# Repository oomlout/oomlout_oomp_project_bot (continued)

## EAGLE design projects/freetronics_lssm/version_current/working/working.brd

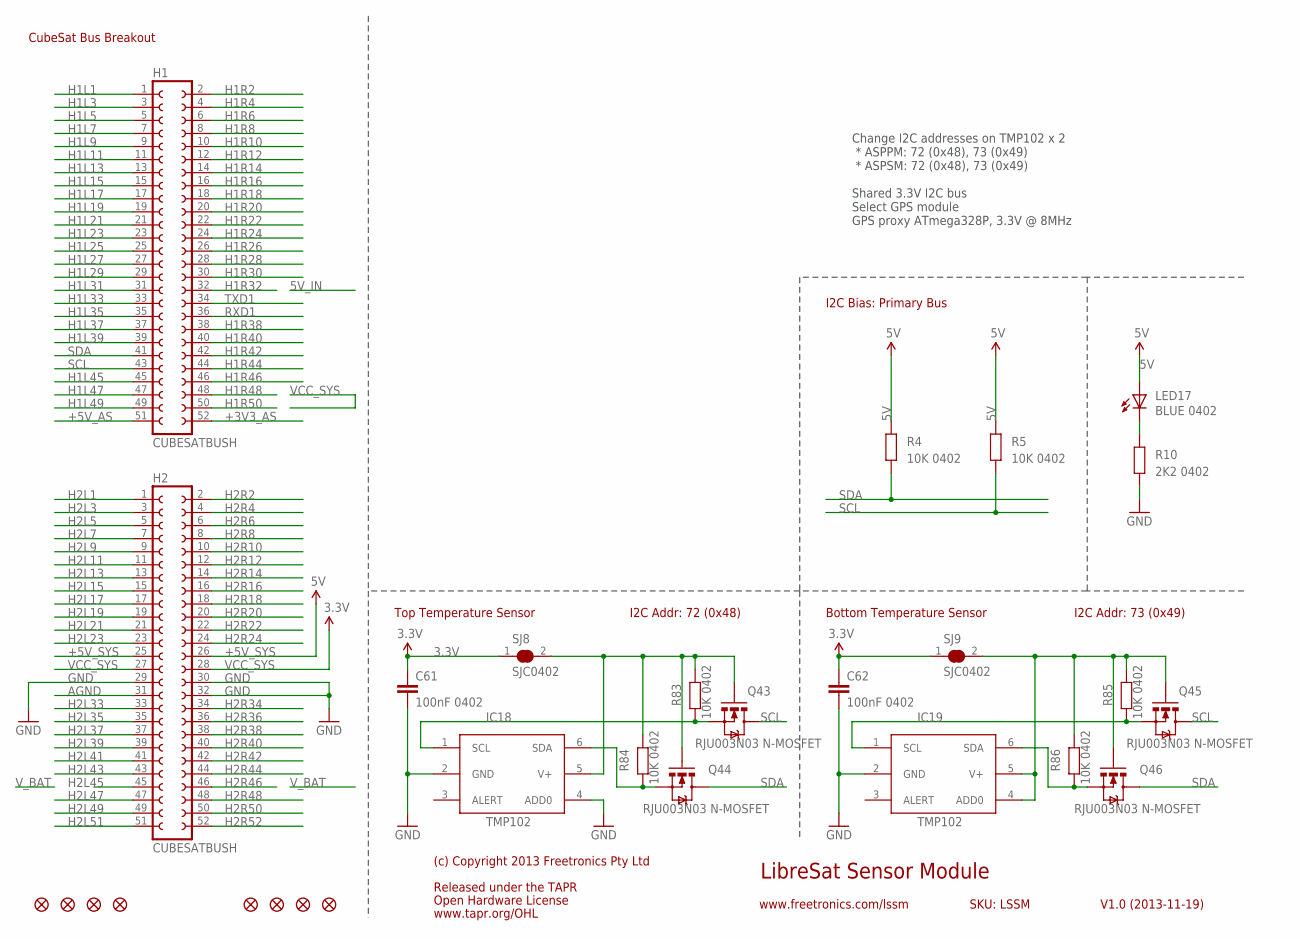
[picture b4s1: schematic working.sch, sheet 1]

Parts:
C61, C62: 100nF 0402; 0402C
FID1, FID2, FID3, FID4, FID5, FID6, FID7, FID8: FIDUCIAL1X2.5; FIDUCIAL-1X2.5
H1, H2: CUBESATBUSH; CUBESATBUS
IC18, IC19: TMP102; SOT563
LED17: BLUE 0402; LED-0402
Q43, Q44, Q45, Q46: RJU003N03 N-MOSFET; SOT32-3
R4, R5, R83, R84, R85, R86: 10K 0402; 0402
R10: 2K2 0402; 0402
SJ8, SJ9: SJC0402; 0402SJC

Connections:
3.3V: C61.1, C62.1, SJ8.1, SJ9.1; also elsewhere on the board
5V: LED17.A, R4.2, R5.2; also elsewhere on the board
+3V3_AS: H1.52
+5V_AS: H1.51
+5V_SYS: H2.25, H2.26
AGND: H2.31
GND: C61.2, C62.2, H2.29, H2.30, H2.32, IC18.2 (GND), IC18.4 (ADD0), IC19.2 (GND), R10.1; also elsewhere on the board
H1L1: H1.1
H1L3: H1.3
H1L5: H1.5
H1L7: H1.7
H1L9: H1.9
H1L11: H1.11
H1L13: H1.13
H1L15: H1.15
H1L17: H1.17
H1L19: H1.19
H1L21: H1.21
H1L23: H1.23
H1L25: H1.25
H1L27: H1.27
H1L29: H1.29
H1L31: H1.31
H1L33: H1.33
H1L35: H1.35
H1L37: H1.37
H1L39: H1.39
H1L45: H1.45
H1L47: H1.47
H1L49: H1.49
H1R2: H1.2
H1R4: H1.4
H1R6: H1.6
H1R8: H1.8
H1R10: H1.10
H1R12: H1.12
H1R14: H1.14
H1R16: H1.16
H1R18: H1.18
H1R20: H1.20
H1R22: H1.22
H1R24: H1.24
H1R26: H1.26
H1R28: H1.28
H1R30: H1.30
H1R32: H1.32
H1R38: H1.38
H1R40: H1.40
H1R42: H1.42
H1R44: H1.44
H1R46: H1.46
H1R48: H1.48
H1R50: H1.50
H2L1: H2.1
H2L3: H2.3
H2L5: H2.5
H2L7: H2.7
H2L9: H2.9
H2L11: H2.11
H2L13: H2.13
H2L15: H2.15
H2L17: H2.17
H2L19: H2.19
H2L21: H2.21
H2L23: H2.23
H2L33: H2.33
H2L35: H2.35
H2L37: H2.37
H2L39: H2.39
H2L41: H2.41
H2L43: H2.43
H2L45: H2.45
H2L47: H2.47
H2L49: H2.49
H2L51: H2.51
H2R2: H2.2
H2R4: H2.4
H2R6: H2.6
H2R8: H2.8
H2R10: H2.10
H2R12: H2.12
H2R14: H2.14
H2R16: H2.16
H2R18: H2.18
H2R20: H2.20
H2R22: H2.22
H2R24: H2.24
H2R34: H2.34
H2R36: H2.36
H2R38: H2.38
H2R40: H2.40
H2R42: H2.42
H2R44: H2.44
H2R46: H2.46
H2R48: H2.48
H2R50: H2.50
H2R52: H2.52
unnamed: LED17.C, R10.2
unnamed: IC18.1 (SCL), Q43.2 (S), R83.1
unnamed: IC18.6 (SDA), Q44.2 (S), R84.1
unnamed: IC19.6 (SDA), Q46.2 (S), R86.1
unnamed: IC19.1 (SCL), Q45.2 (S), R85.1
unnamed: IC18.5 (V+), Q43.1 (G), Q44.1 (G), R83.2, R84.2, SJ8.2
unnamed: IC19.4 (ADD0), IC19.5 (V+), Q45.1 (G), Q46.1 (G), R85.2, R86.2, SJ9.2
RXD1: H1.36; also elsewhere on the board
SCL: H1.43, Q43.3 (D), Q45.3 (D), R5.1; also elsewhere on the board
SDA: H1.41, Q44.3 (D), Q46.3 (D), R4.1; also elsewhere on the board
TXD1: H1.34; also elsewhere on the board
VCC_SYS: H2.27, H2.28

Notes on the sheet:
LibreSat Sensor Module
V1.0 (2013-11-19)
www.freetronics.com/lssm
SKU: LSSM
CubeSat Bus Breakout
Released under the TAPR
Open Hardware License
www.tapr.org/OHL
(c) Copyright 2013 Freetronics Pty Ltd
I2C Bias: Primary Bus
Top Temperature Sensor
Bottom Temperature Sensor
I2C Addr: 72 (0x48)
I2C Addr: 73 (0x49)
Change I2C addresses on TMP102 x 2 * ASPPM: 72 (0x48), 73 (0x49) * ASPSM: 72 (0x48), 73 (0x49) Shared 3.3V I2C bus Select GPS module GPS proxy ATmega328P, 3.3V @ 8MHz

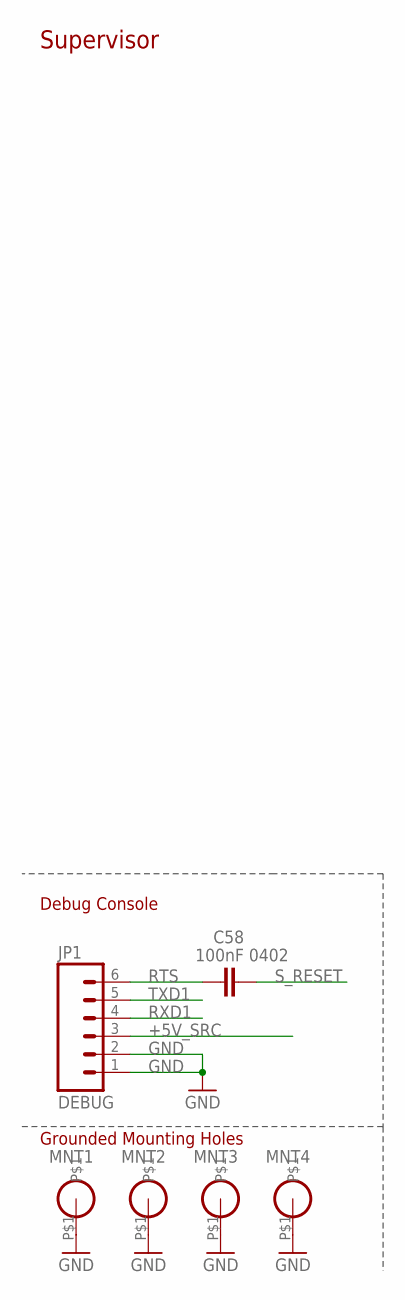
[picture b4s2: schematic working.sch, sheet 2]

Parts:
C58: 100nF 0402; 0402C
JP1: DEBUG; MOLEX-1X6-RA
MNT1, MNT2, MNT3, MNT4: HOLE3.2MM; HOLE32

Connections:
+5V_SRC: JP1.3
GND: JP1.1, JP1.2, MNT1.P$1, MNT2.P$1, MNT3.P$1, MNT4.P$1; also elsewhere on the board
RTS: C58.1, JP1.6
RXD1: JP1.4; also elsewhere on the board
S_RESET: C58.2
TXD1: JP1.5; also elsewhere on the board

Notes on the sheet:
Supervisor
Grounded Mounting Holes
Debug Console

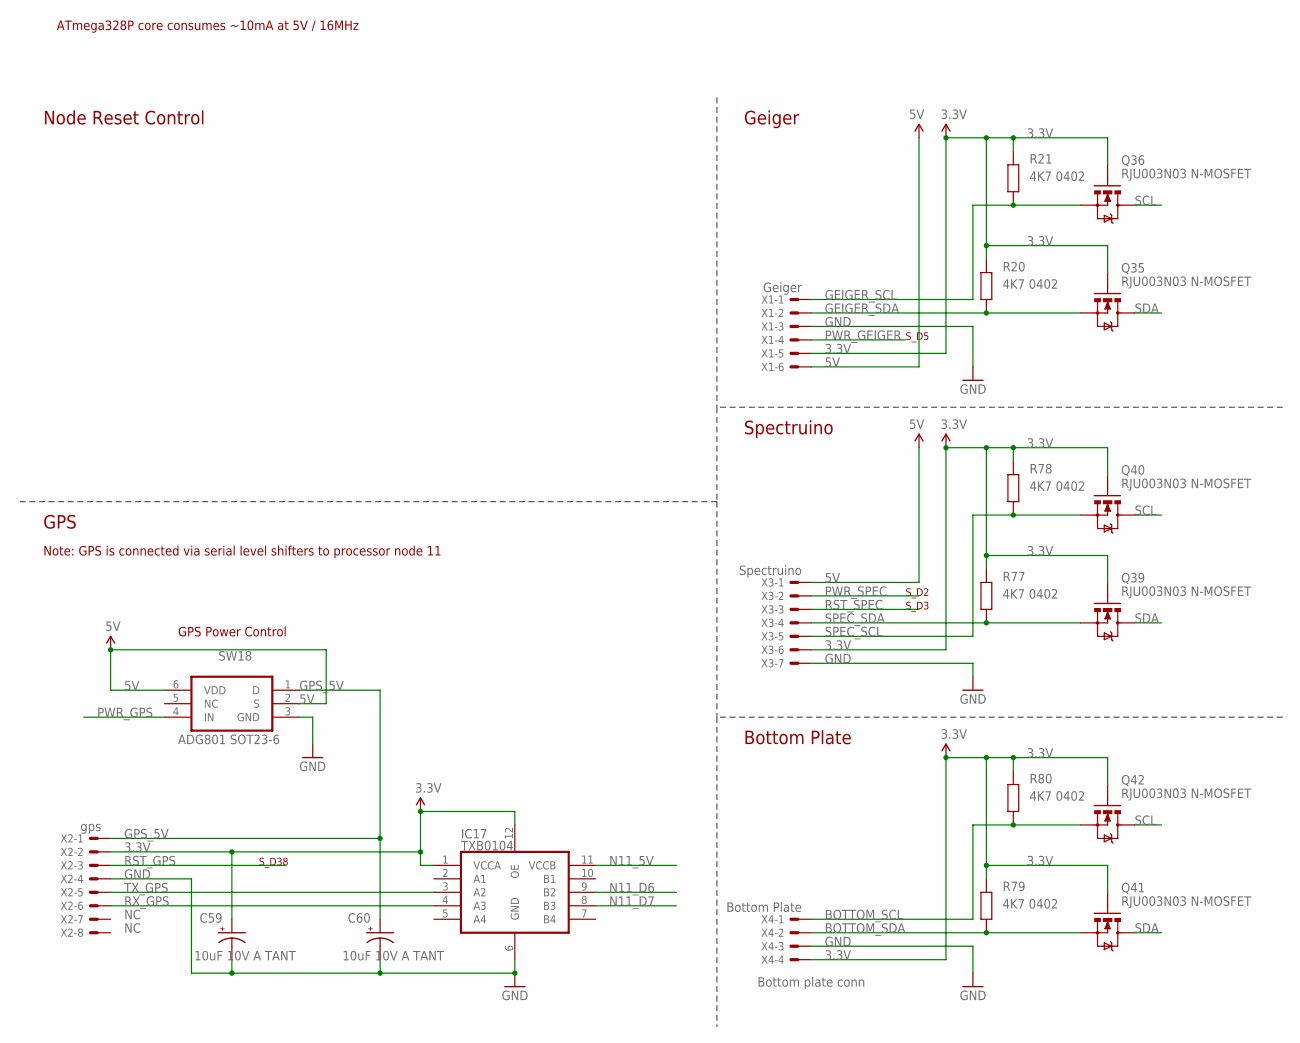
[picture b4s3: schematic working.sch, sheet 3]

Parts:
C59, C60: 10uF 10V A TANT; EIA3216
IC17: TXB0104; QFN-12
Q35, Q36, Q39, Q40, Q41, Q42: RJU003N03 N-MOSFET; SOT32-3
R20, R21, R77, R78, R79, R80: 4K7 0402; 0402
SW18: ADG801 SOT23-6; SOT23-6
X1: Geiger; 53398-06
X2: gps; 53398-08
X3: Spectruino; 53398-07
X4: Bottom Plate; 53398-04

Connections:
3.3V: C59.A (+), IC17.1 (VCCA), IC17.12 (OE), Q35.1 (G), Q36.1 (G), Q39.1 (G), Q40.1 (G), Q41.1 (G), Q42.1 (G), R20.2, R21.2, R77.2, R78.2, R79.2, R80.2, X1.5, X2.2, X3.6, X4.4; also elsewhere on the board
5V: SW18.2 (S), SW18.6 (VDD), X1.6, X3.1; also elsewhere on the board
BOTTOM_SCL: Q42.2 (S), R80.1, X4.1
BOTTOM_SDA: Q41.2 (S), R79.1, X4.2
GEIGER_SCL: Q36.2 (S), R21.1, X1.1
GEIGER_SDA: Q35.2 (S), R20.1, X1.2
GND: C59.C (-), C60.C (-), IC17.6 (GND), SW18.3 (GND), X1.3, X2.4, X3.7, X4.3; also elsewhere on the board
GPS_5V: C60.A (+), SW18.1 (D), X2.1
N11_5V: IC17.11 (VCCB); also elsewhere on the board
N11_D6: IC17.9 (B2); also elsewhere on the board
N11_D7: IC17.8 (B3); also elsewhere on the board
PWR_GEIGER: X1.4
PWR_GPS: SW18.4 (IN)
PWR_SPEC: X3.2
RST_GPS: X2.3
RST_SPEC: X3.3
RX_GPS: IC17.4 (A3), X2.6
SCL: Q36.3 (D), Q40.3 (D), Q42.3 (D); also elsewhere on the board
SDA: Q35.3 (D), Q39.3 (D), Q41.3 (D); also elsewhere on the board
SPEC_SCL: Q40.2 (S), R78.1, X3.5
SPEC_SDA: Q39.2 (S), R77.1, X3.4
TX_GPS: IC17.3 (A2), X2.5

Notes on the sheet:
Node Reset Control
Bottom plate conn
Geiger
Spectruino
Bottom Plate
GPS
Note: GPS is connected via serial level shifters to processor node 11
S_D3
S_D2
S_D5
ATmega328P core consumes ~10mA at 5V / 16MHz
S_D38
GPS Power Control

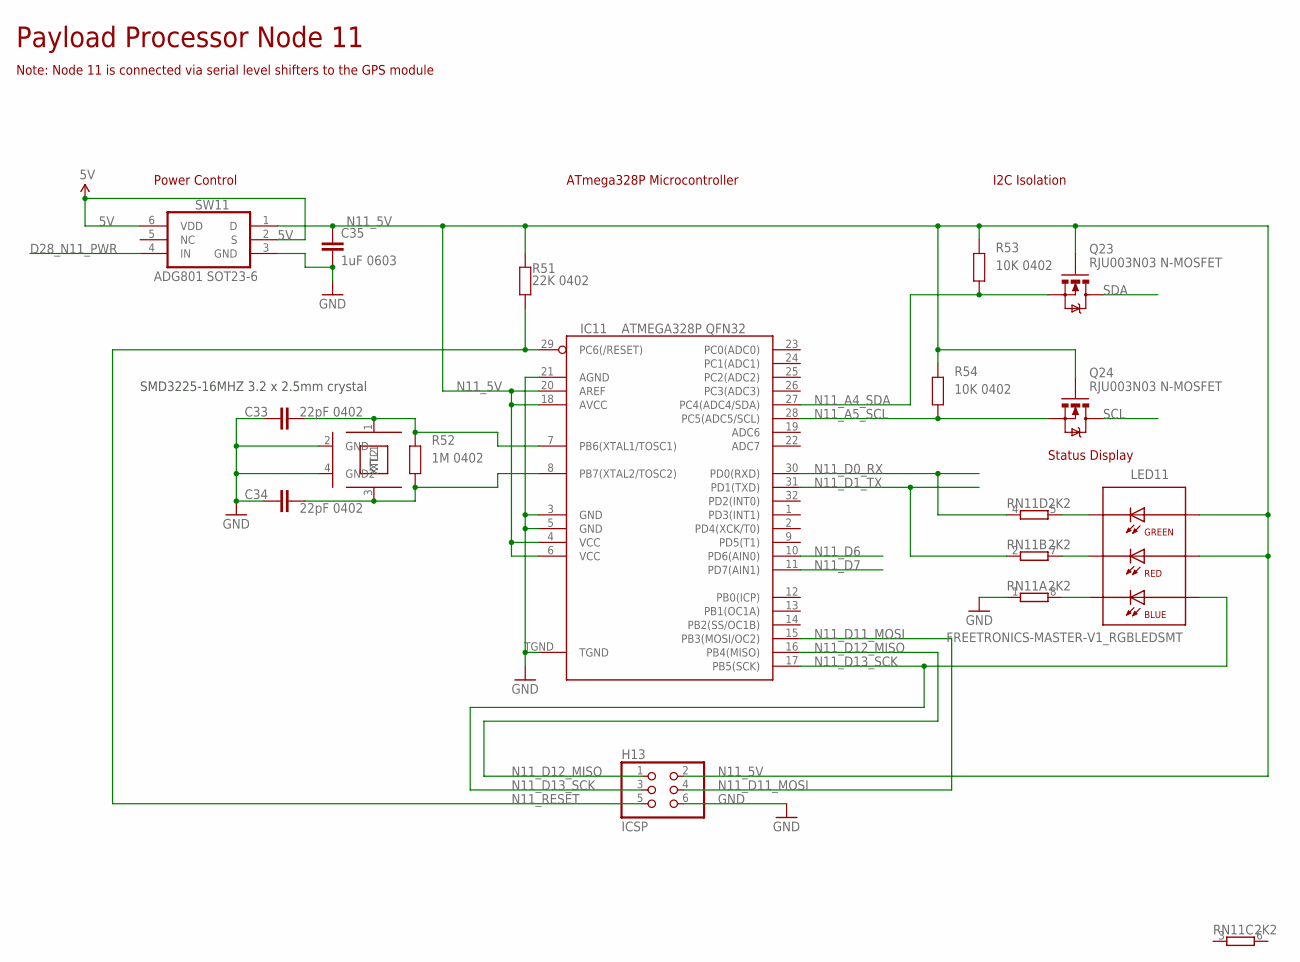
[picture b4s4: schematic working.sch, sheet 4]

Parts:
C33, C34: 22pF 0402; 0402C
C35: 1uF 0603; C0603
H13: ICSP; M2X3-2MM
IC11: ATMEGA328P QFN32; MLF32
LED11: FREETRONICS-MASTER-V1_RGBLEDSMT; FREETRONICS-MASTER-V1_19-337
Q23, Q24: RJU003N03 N-MOSFET; SOT32-3
R51: 22K 0402; 0402
R52: 1M 0402; 0402
R53, R54: 10K 0402; 0402
RN11: 2K2; CAY16
SW11: ADG801 SOT23-6; SOT23-6
XTL11: SMD3225-8MHZ 3.2 x 2.5mm crystal; CRYSTAL-SMD-3X2

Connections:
5V: SW11.2 (S), SW11.6 (VDD); also elsewhere on the board
D28_N11_PWR: SW11.4 (IN)
GND: C33.1, C34.1, C35.2, H13.6, IC11.3 (GND), IC11.5 (GND), IC11.21 (AGND), IC11.TGND, RN11.1, SW11.3 (GND), XTL11.2 (GND), XTL11.4 (GND2); also elsewhere on the board
N11_5V: C35.1, H13.2, IC11.4 (VCC), IC11.6 (VCC), IC11.18 (AVCC), IC11.20 (AREF), LED11.5 (A-R), LED11.6 (A-G), Q23.1 (G), Q24.1 (G), R51.2, R53.2, R54.2, SW11.1 (D); also elsewhere on the board
N11_A4_SDA: IC11.27 (PC4(ADC4/SDA)), Q23.2 (S), R53.1
N11_A5_SCL: IC11.28 (PC5(ADC5/SCL)), Q24.2 (S), R54.1
N11_D0_RX: IC11.30 (PD0(RXD)), RN11.4 (1)
N11_D1_TX: IC11.31 (PD1(TXD)), RN11.2 (1)
N11_D6: IC11.10 (PD6(AIN0)); also elsewhere on the board
N11_D7: IC11.11 (PD7(AIN1)); also elsewhere on the board
N11_D11_MOSI: H13.4, IC11.15 (PB3(MOSI/OC2))
N11_D12_MISO: H13.1, IC11.16 (PB4(MISO))
N11_D13_SCK: H13.3, IC11.17 (PB5(SCK)), LED11.4 (A-B)
N11_RESET: H13.5, IC11.29 (PC6(/RESET)), R51.1
unnamed: C34.2, IC11.8 (PB7(XTAL2/TOSC2)), R52.1, XTL11.3 (XTL2)
unnamed: C33.2, IC11.7 (PB6(XTAL1/TOSC1)), R52.2, XTL11.1 (XTL1)
unnamed: LED11.2 (C-R), RN11.7 (2)
unnamed: LED11.1 (C-B), RN11.8 (2)
unnamed: LED11.3 (C-G), RN11.5 (2)
SCL: Q24.3 (D); also elsewhere on the board
SDA: Q23.3 (D); also elsewhere on the board

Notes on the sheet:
Payload Processor Node 11
ATmega328P Microcontroller
I2C Isolation
Status Display
Power Control
SMD3225-16MHZ 3.2 x 2.5mm crystal
Note: Node 11 is connected via serial level shifters to the GPS module

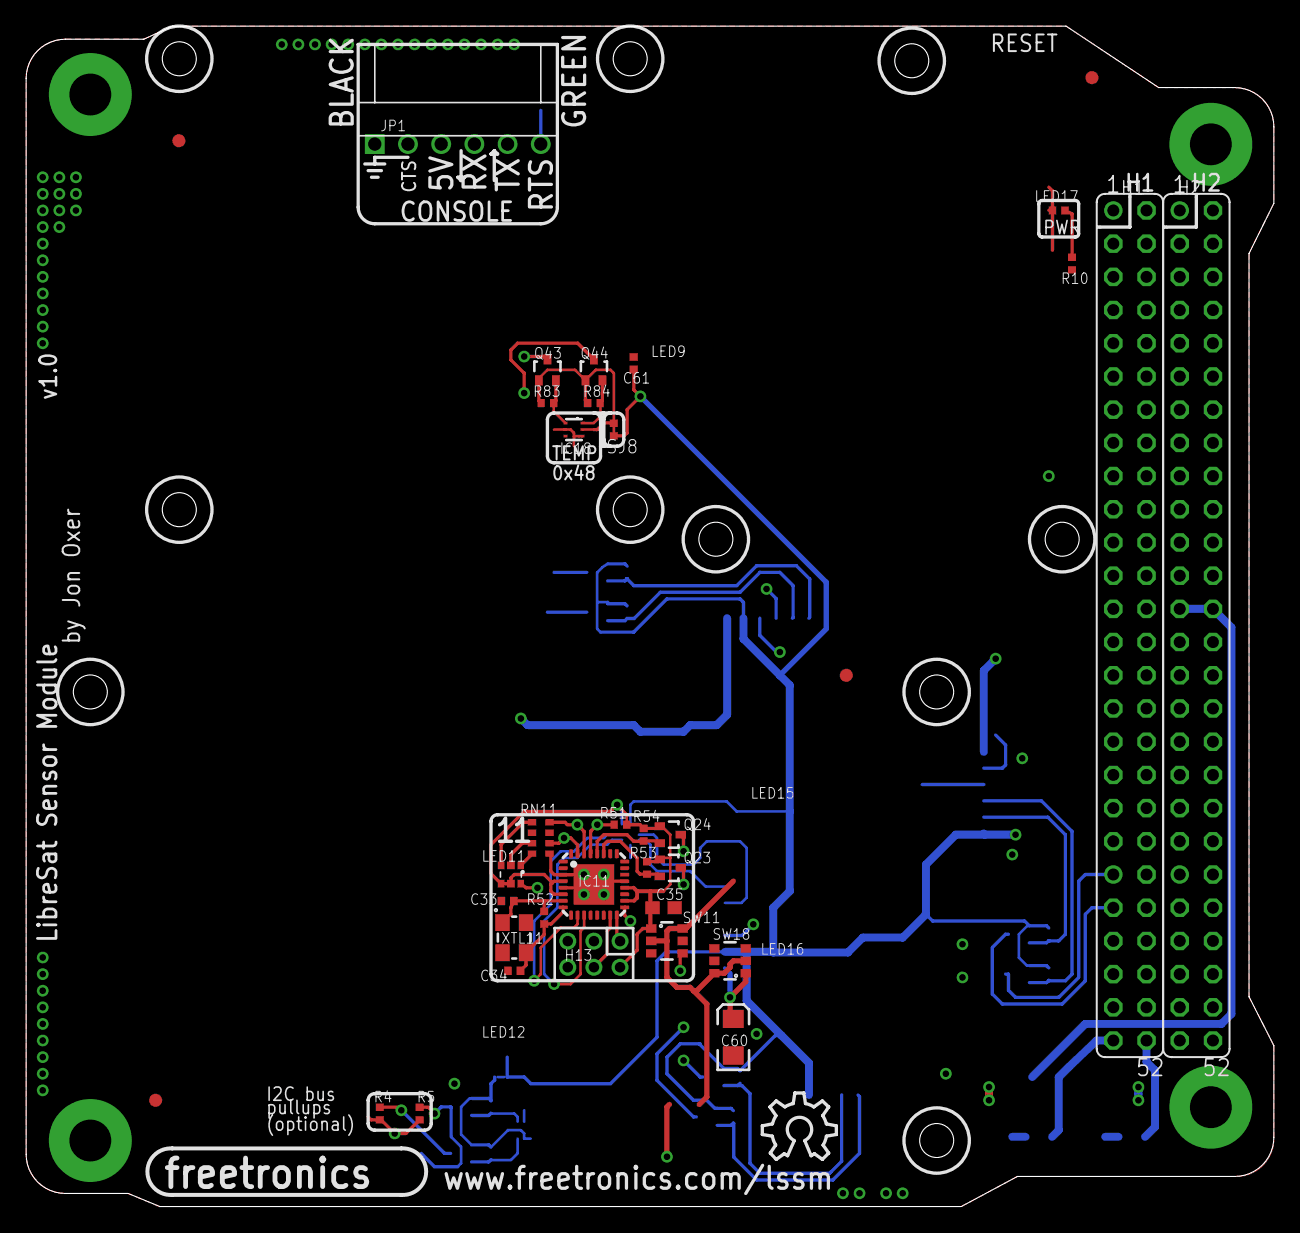
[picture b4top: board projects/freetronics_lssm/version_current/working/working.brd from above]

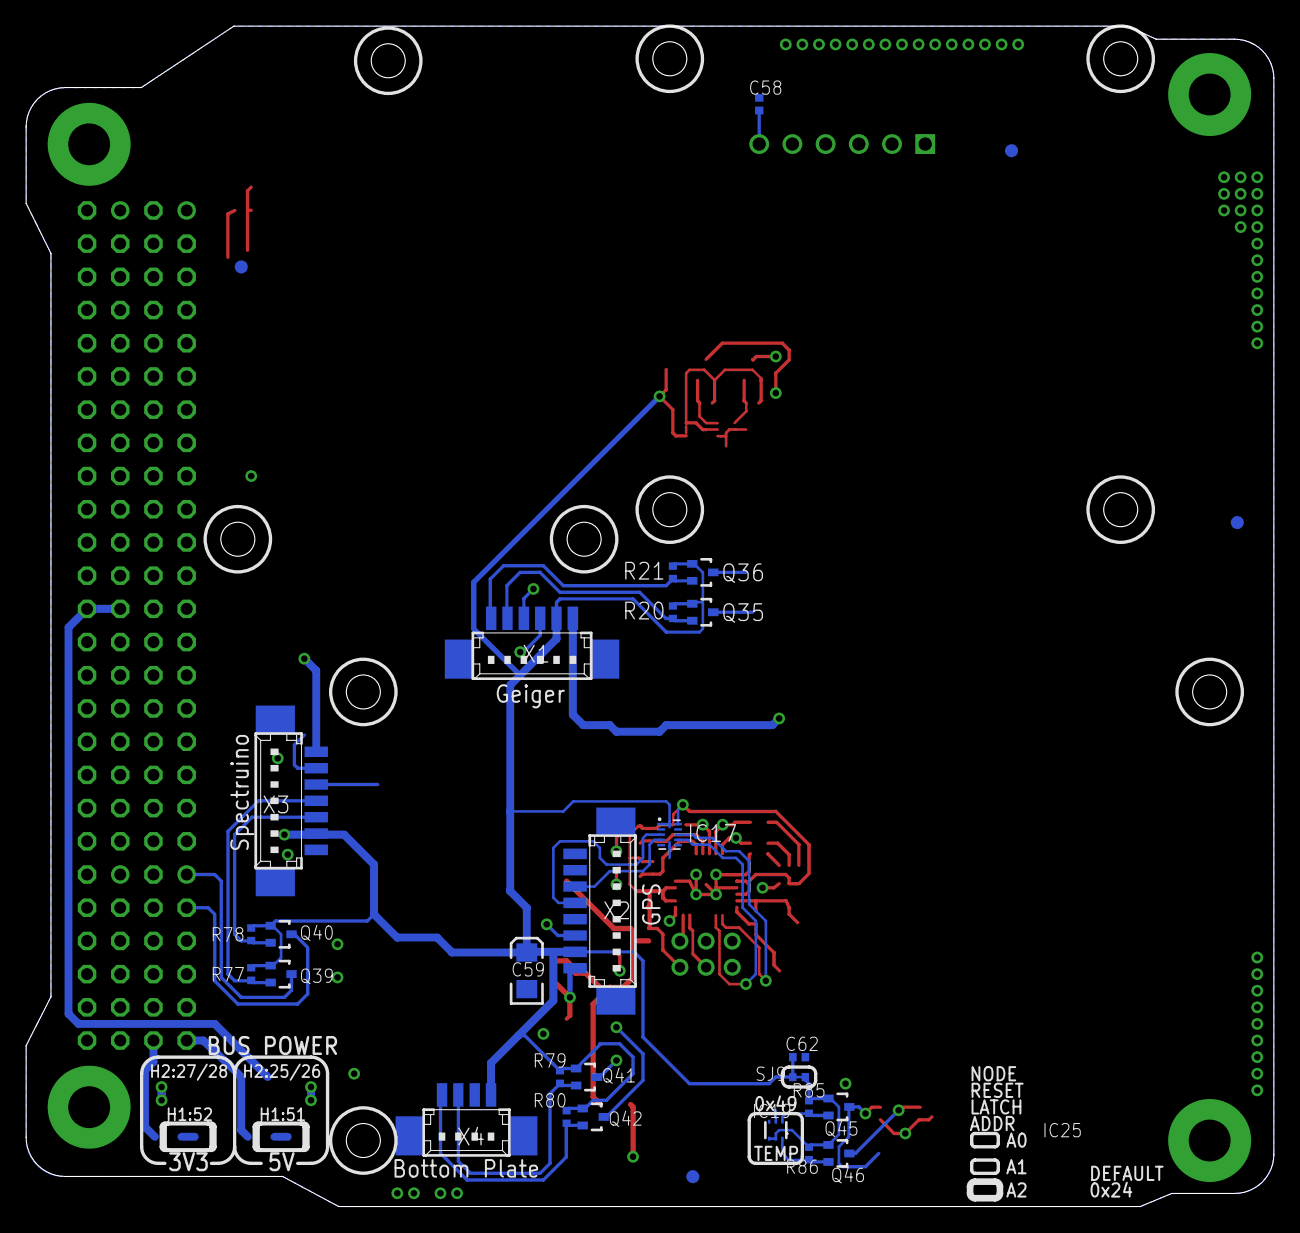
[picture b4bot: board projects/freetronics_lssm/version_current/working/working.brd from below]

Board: 4 copper layers, 95.5 x 90.3 mm, 70 parts (30 on the bottom side), 42 nets.

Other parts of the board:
U$33: OSHW_10X200_NOTEXT

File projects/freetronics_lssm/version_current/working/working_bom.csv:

"Id";"Designator";"Footprint";"Quantity";"Designation";"Supplier and ref";
1;"Q23,Q44,Q43,Q24,Q42,Q36,Q46,Q35,Q41,Q40,Q39,Q45";"SOT32-3";12;"RJU003N03 N-MOSFET";;;
2;"RN11";"CAY16";1;"2K2";;;
3;"MNT1,MNT2,MNT3,MNT4";"HOLE32";4;"HOLE3.2MM";;;
4;"@HOLE6,@HOLE5,@HOLE9,@HOLE4,@HOLE2,@HOLE3,@HOLE8,@HOLE7,@HOLE1,@HOLE0";"";10;"";;;
5;"R53,R5,R54,R84,R83,R4,R85,R86";"0402";8;"10K 0402";;;
6;"C60,C59";"EIA3216";2;"10uF 10V A TANT";;;
7;"LED11";"FREETRONICS-MASTER-V1_19-337";1;"FREETRONICS-MASTER-V1_RGBLEDSMT";;;
8;"R52";"0402";1;"1M 0402";;;
9;"C35";"C0603";1;"1uF 0603";;;
10;"IC18,IC19";"SOT563";2;"TMP102";;;
11;"LED17";"LED-0402";1;"BLUE 0402";;;
12;"FID2,FID4,FID1,FID3,FID8,FID5,FID7,FID6";"FIDUCIAL-1X2.5";8;"FIDUCIAL1X2.5";;;
13;"SW18,SW11";"SOT23-6";2;"ADG801 SOT23-6";;;
14;"C61,C62,C58";"0402C";3;"100nF 0402";;;
15;"H1,H2";"CUBESATBUS";2;"CUBESATBUSH";;;
16;"XTL11";"CRYSTAL-SMD-3X2";1;"SMD3225-8MHZ 3.2 x 2.5mm crystal";;;
17;"C34,C33";"0402C";2;"22pF 0402";;;
18;"R51";"0402";1;"22K 0402";;;
19;"H13";"M2X3-2MM";1;"ICSP";;;
20;"R10";"0402";1;"2K2 0402";;;
21;"SJ8,SJ9";"0402SJC";2;"SJC0402";;;
22;"JP1";"MOLEX-1X6-RA";1;"DEBUG";;;
23;"U$33";"OSHW_10X200_NOTEXT";1;"";;;
24;"IC11";"MLF32";1;"ATMEGA328P QFN32";;;
25;"R21,R80,R79,R78,R20,R77";"0402";6;"4K7 0402";;;
26;"X1";"53398-06";1;"Geiger";;;
27;"X4";"53398-04";1;"Bottom Plate";;;
28;"IC17";"QFN-12";1;"TXB0104";;;
29;"X2";"53398-08";1;"gps";;;
30;"X3";"53398-07";1;"Spectruino";;;

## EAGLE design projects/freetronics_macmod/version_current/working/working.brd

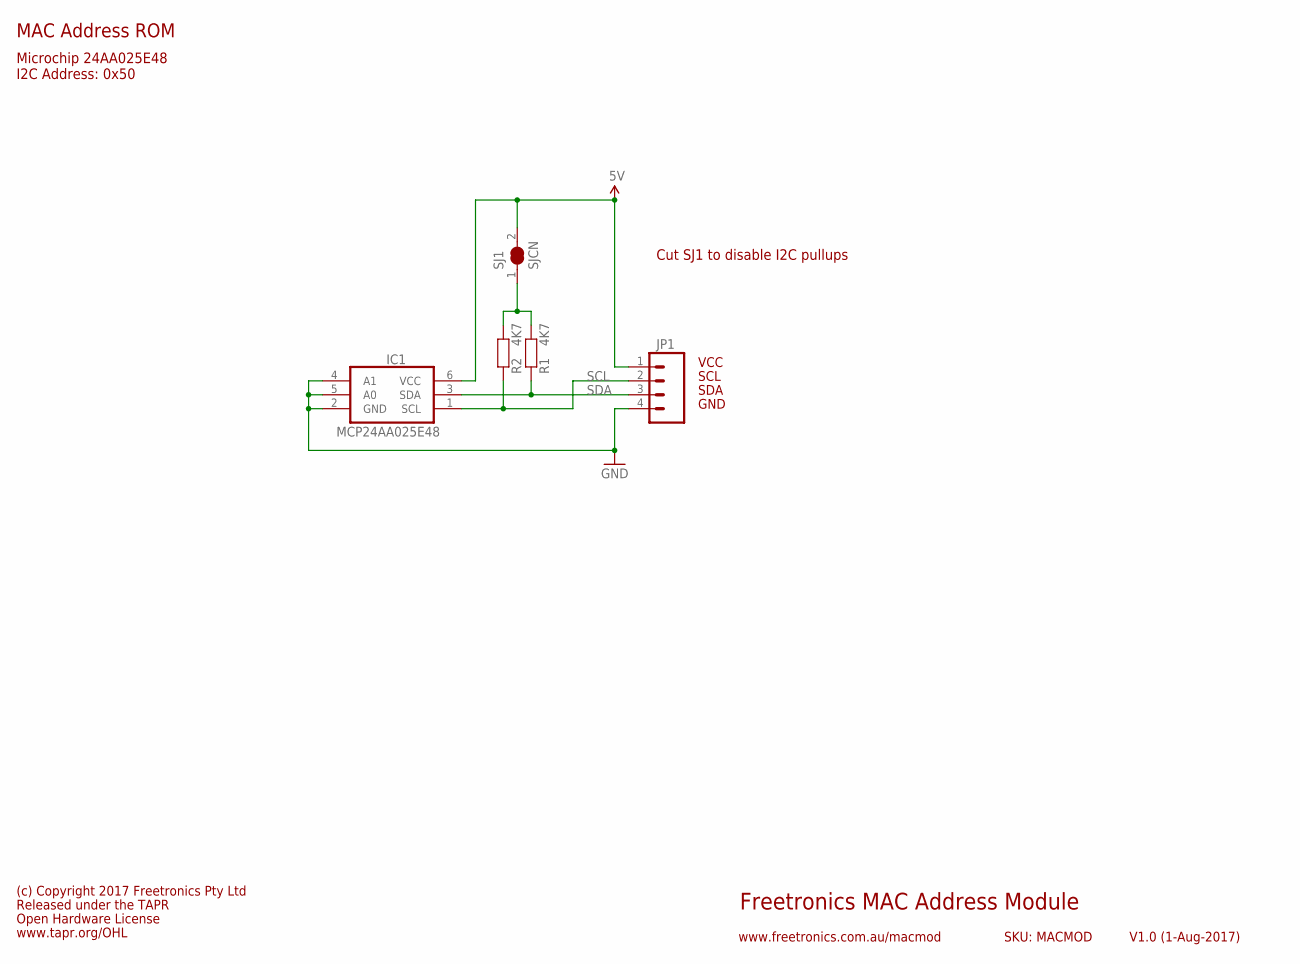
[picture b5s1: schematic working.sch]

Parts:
IC1: MCP24AA025E48; SOT23-6
JP1: M04PTH; 1X04
R1, R2: 4K7; 0603
SJ1: SJCN; SJC

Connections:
5V: IC1.6 (VCC), JP1.1, SJ1.2
GND: IC1.2 (GND), IC1.4 (A1), IC1.5 (A0), JP1.4
unnamed: R1.2, R2.2, SJ1.1
SCL: IC1.1 (SCL), JP1.2, R2.1
SDA: IC1.3 (SDA), JP1.3, R1.1

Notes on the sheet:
Freetronics MAC Address Module
V1.0 (1-Aug-2017)
www.freetronics.com.au/macmod
SKU: MACMOD
Microchip 24AA025E48 I2C Address: 0x50
MAC Address ROM
Released under the TAPR
Open Hardware License
www.tapr.org/OHL
(c) Copyright 2017 Freetronics Pty Ltd
VCC
SCL
SDA
GND
Cut SJ1 to disable I2C pullups

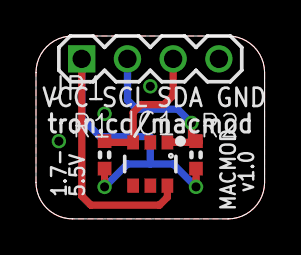
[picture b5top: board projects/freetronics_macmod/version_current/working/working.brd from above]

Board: 2 copper layers, 12.7 x 10.2 mm, 5 parts (1 on the bottom side), 5 nets.

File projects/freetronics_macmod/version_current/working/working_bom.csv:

"Id";"Designator";"Footprint";"Quantity";"Designation";"Supplier and ref";
1;"JP1";"1X04";1;"";;;
2;"R1,R2";"0603";2;"4K7";;;
3;"IC1";"SOT23-6";1;"MCP24AA025E48";;;
4;"SJ1";"SJC";1;"SJCN";;;

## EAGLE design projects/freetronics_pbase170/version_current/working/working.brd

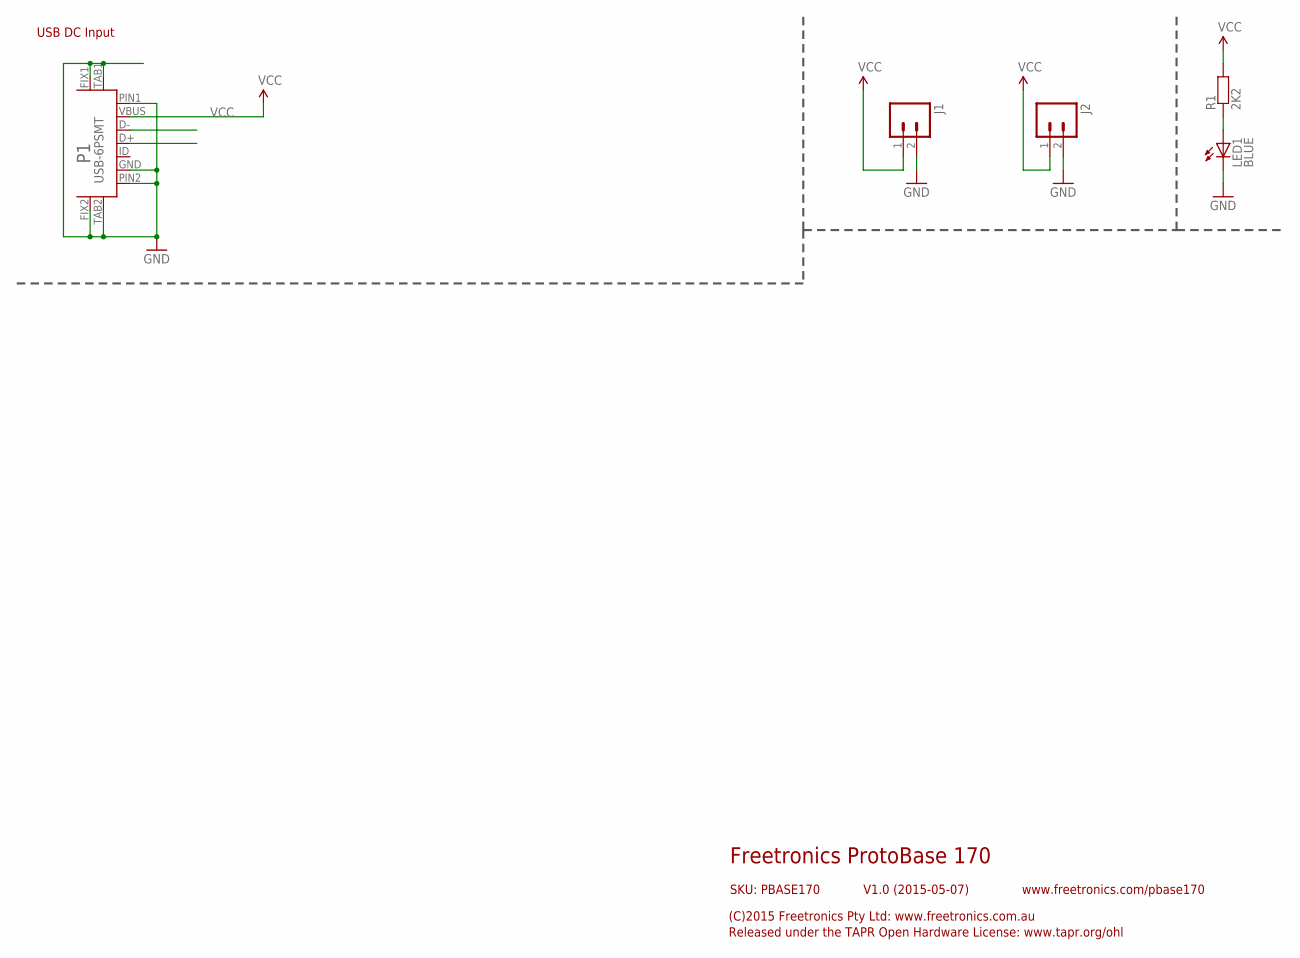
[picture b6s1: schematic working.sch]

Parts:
J1, J2: M02PTH; 1X02
LED1: BLUE; LED-0603
P1: USB-6PSMT; USB-MICROB-MB05PMXX
R1: 2K2; 0603

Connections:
GND: J1.2, J2.2, LED1.C, P1.FIX1, P1.FIX2, P1.GND, P1.PIN1, P1.PIN2, P1.TAB1, P1.TAB2
unnamed: LED1.A, R1.1
VCC: J1.1, J2.1, P1.VBUS, R1.2

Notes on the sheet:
USB DC Input
Freetronics ProtoBase 170
V1.0 (2015-05-07)
SKU: PBASE170
(C)2015 Freetronics Pty Ltd: www.freetronics.com.au
Released under the TAPR Open Hardware License: www.tapr.org/ohl
www.freetronics.com/pbase170

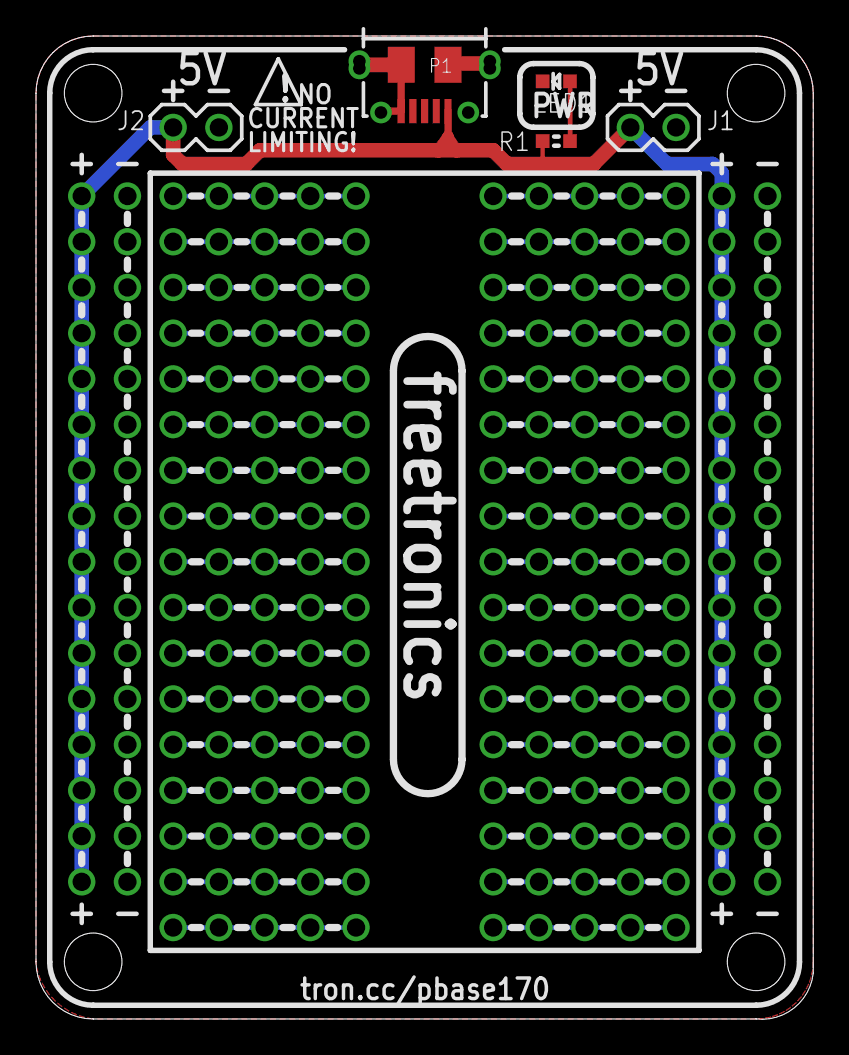
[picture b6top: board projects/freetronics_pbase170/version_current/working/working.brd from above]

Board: 2 copper layers, 43.2 x 54.6 mm, 5 parts (0 on the bottom side), 3 nets.

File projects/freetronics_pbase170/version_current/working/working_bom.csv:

"Id";"Designator";"Footprint";"Quantity";"Designation";"Supplier and ref";
1;"LED1";"LED-0603";1;"BLUE";;;
2;"@HOLE1,@HOLE0,@HOLE3,@HOLE2";"";4;"";;;
3;"R1";"0603";1;"2K2";;;
4;"J2,J1";"1X02";2;"";;;
5;"P1";"USB-MICROB-MB05PMXX";1;"USB-6PSMT";;;
